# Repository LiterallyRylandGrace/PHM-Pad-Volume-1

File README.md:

Please refer to the README inside the PHMPAD Vol. 1. I'm not too sure how to delete this one.

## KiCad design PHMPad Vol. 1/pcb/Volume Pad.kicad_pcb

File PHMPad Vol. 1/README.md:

# PHM Pad Vol. 1

The PHM Pad Vol. 1 is a macropad designed to compensate for the flaw of many keyboard being the absence of volume-related controls. Inspired by the science-fiction world of Project Hail Mary, it harbours the PHM logo as well as the quote from the movie "Grace Rocky Save Stars". It has six keys as follows, from left to right for the first row and then the second. Previous, Pause/Play, Next, Mute/Unmute, Volume Down, Volume Up.

## Features
- A screwable cover and main body. You don't need much more. Function over form, as they say.
- 6 keys. No more, no less.

## CAD Model
4 Screws and you're good. How innovative, am I right? You get a bottom and a top. The design is made to match with my computer case, so it's not guaranteed to work (aesthetically) with yours. To be fair, it is my very first CAD model so I think it doesn't look all to shabby.

Made in Fusion 360.
Works. Hopefully.

## PCB
PCB TIME! I decided to venture a bit away from the tutorial that is the HackPad. My confidence towards anything that I did is almost null which means you could say that this project is held up by hopes and prayers.

Instead of making a regular matrix with rows and columns I decided to be original and opted for a direct pin configuration matrix.

## Firmware

[QMK](https://qmk.fm/) is used for all of the firmware. I am very lucky they have a tutorial.

6 keys forming the 3 by 2 format. yay.

## BOM
- 6 Cherry MX Switches
- 6 DSA Keycaps
- 4 M3x12mm SHCS Bolts
- 1 XIAO RP2040
- 1 Case (main body and top lid)

## Extra
Believe in the Hail Mary.

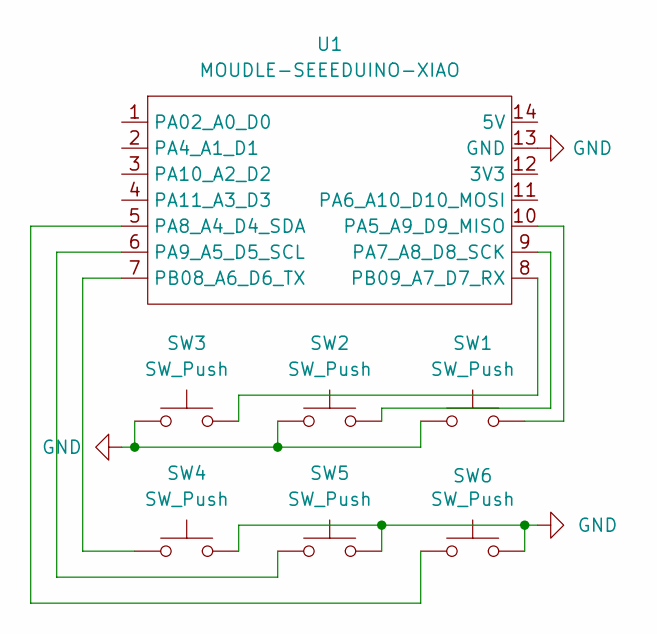
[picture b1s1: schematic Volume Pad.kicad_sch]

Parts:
SW1, SW2, SW3, SW4, SW5, SW6: SW_Push; SW_Cherry_MX_1.00u_PCB
U1: MOUDLE-SEEEDUINO-XIAO; XIAO-Generic-Hybrid-14P-2.54-21X17.8MM

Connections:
GND: SW1.1, SW2.1, SW3.1, SW4.2, SW5.2, SW6.2, U1.13 (GND)
unnamed: SW1.2, U1.10 (PA5_A9_D9_MISO)
unnamed: SW2.2, U1.9 (PA7_A8_D8_SCK)
unnamed: SW6.1, U1.5 (PA8_A4_D4_SDA)
unnamed: SW5.1, U1.6 (PA9_A5_D5_SCL)
unnamed: SW4.1, U1.7 (PB08_A6_D6_TX)
unnamed: SW3.2, U1.8 (PB09_A7_D7_RX)

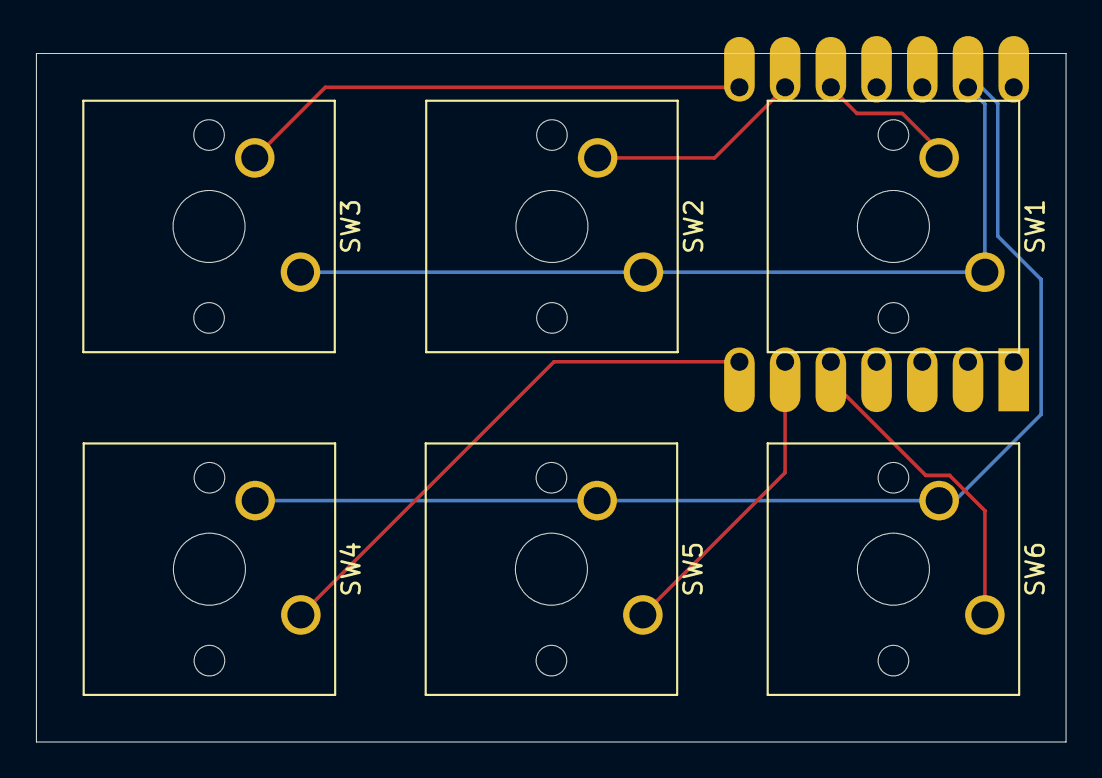
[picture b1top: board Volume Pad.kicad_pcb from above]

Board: 2 copper layers, 57.2 x 38.2 mm, 7 parts (1 on the bottom side), 7 nets.
